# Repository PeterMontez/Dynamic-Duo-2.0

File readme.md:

# Web Application for a Tooling Storage System

Web application with the main goal of aiding people on the workshop to better keep up with the ever-changing position of their tools.

## About the project

Using EJS, JS and CSS, the application is very intuitive and simple to use, and alongside a RFID card reader allows the workers to remove or return tools to their correct cabinet and drawer.

Using mysql and sequelize to handle the data, the user can easily find the tool they want with very descriptive cards.
## Authors

- [@PeterMontez](https://github.com/PeterMontez)
- [@NycollasSobolevski](https://github.com/NycollasSobolevski)

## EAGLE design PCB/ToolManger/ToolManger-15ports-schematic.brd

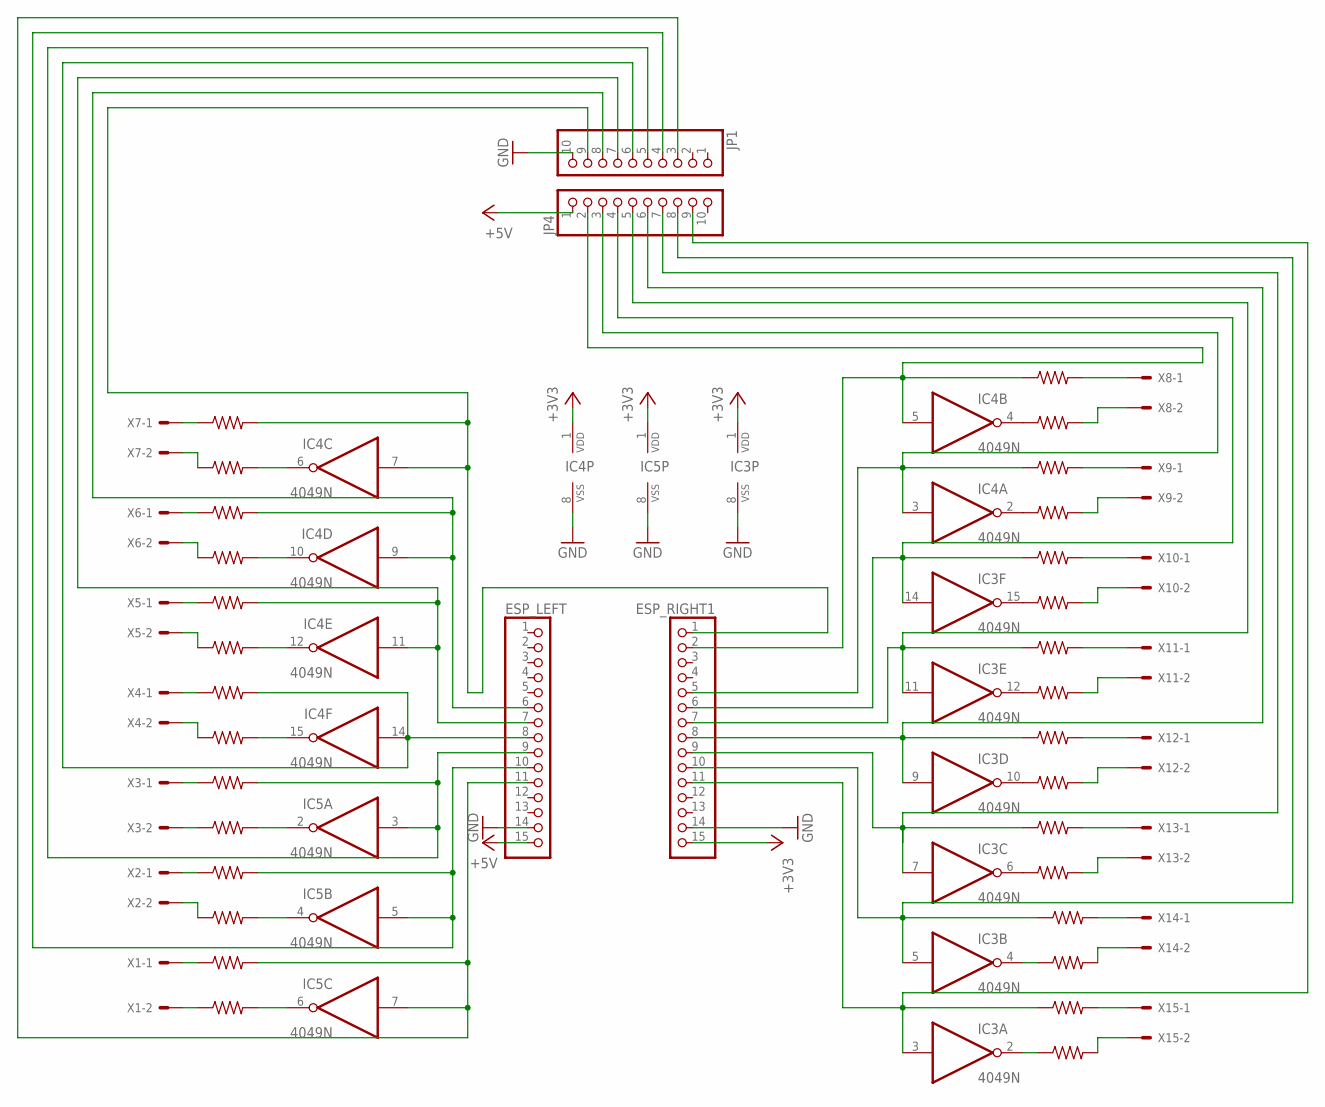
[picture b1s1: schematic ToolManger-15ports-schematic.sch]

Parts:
ESP_LEFT: PINHD-1X15; 1X15
ESP_RIGHT1: PINHD-1X15; 1X15
IC3, IC4, IC5: 4049N; DIL16
JP1, JP4: PINHD-1X10; 1X10
R1, R2, R3, R4, R5, R6, R7, R8, R9, R10, R11, R12, R13, R14, R15, R16, R17, R18, R19, R21, R22, R23, R24, R25, R26, R27, R28, R29, R30, R32: R-US_0207/12; 0207/12
X1, X2, X3, X4, X5, X6, X7, X8, X9, X10, X11, X12, X13, X14, X15: KK-156-2

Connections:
+3V3: ESP_RIGHT1.15, IC3.1 (VDD), IC4.1 (VDD), IC5.1 (VDD)
+5V: ESP_LEFT.15, JP4.1
GND: ESP_LEFT.14, ESP_RIGHT1.14, IC3.8 (VSS), IC4.8 (VSS), IC5.8 (VSS), JP1.10
unnamed: ESP_LEFT.6, IC4.9 (I), JP1.8, R30.2
unnamed: IC3.2 (O), R6.1
unnamed: R6.2, X15.2
unnamed: ESP_LEFT.7, IC4.11 (I), JP1.7, R18.2
unnamed: R18.1, X5.1
unnamed: R1.2, X15.1
unnamed: IC3.4 (O), R2.1
unnamed: R3.2, X14.1
unnamed: R2.2, X14.2
unnamed: ESP_RIGHT1.10, IC3.5 (I), JP4.8, R3.1
unnamed: IC3.6 (O), R4.1
unnamed: IC3.10 (O), R7.1
unnamed: IC3.15 (O), R11.1
unnamed: IC3.12 (O), R9.1
unnamed: R5.2, X13.1
unnamed: R4.2, X13.2
unnamed: R16.2, X8.1
unnamed: R8.2, X12.1
unnamed: R7.2, X12.2
unnamed: R9.2, X11.2
unnamed: R10.2, X11.1
unnamed: R11.2, X10.2
unnamed: R12.2, X10.1
unnamed: R13.2, X9.2
unnamed: R14.2, X9.1
unnamed: R15.2, X8.2
unnamed: ESP_RIGHT1.11, IC3.3 (I), JP4.9, R1.1
unnamed: IC4.2 (O), R13.1
unnamed: ESP_RIGHT1.9, IC3.7 (I), JP4.7, R5.1
unnamed: ESP_RIGHT1.8, IC3.9 (I), JP4.6, R8.1
unnamed: ESP_RIGHT1.7, IC3.11 (I), JP4.5, R10.1
unnamed: ESP_RIGHT1.6, IC3.14 (I), JP4.4, R12.1
unnamed: IC4.4 (O), R15.1
unnamed: ESP_RIGHT1.2, IC4.5 (I), JP4.2, R16.1
unnamed: ESP_RIGHT1.5, IC4.3 (I), JP4.3, R14.1
unnamed: ESP_LEFT.8, IC4.14 (I), JP1.6, R27.2
unnamed: ESP_LEFT.9, IC5.3 (I), JP1.5, R25.2
unnamed: ESP_LEFT.10, IC5.5 (I), JP1.4, R23.2
unnamed: ESP_LEFT.11, IC5.7 (I), JP1.3, R21.2
unnamed: ESP_RIGHT1.1, IC4.7 (I), JP1.9, R32.2
unnamed: R32.1, X7.1
unnamed: R21.1, X1.1
unnamed: IC4.6 (O), R19.2
unnamed: R23.1, X2.1
unnamed: R25.1, X3.1
unnamed: IC5.4 (O), R22.2
unnamed: IC5.2 (O), R24.2
unnamed: IC4.12 (O), R28.2
unnamed: R24.1, X3.2
unnamed: R27.1, X4.1
unnamed: R28.1, X5.2
unnamed: R29.1, X6.2
unnamed: R30.1, X6.1
unnamed: R19.1, X7.2
unnamed: IC4.10 (O), R29.2
unnamed: IC5.6 (O), R17.2
unnamed: IC4.15 (O), R26.2
unnamed: R26.1, X4.2
unnamed: R22.1, X2.2
unnamed: R17.1, X1.2

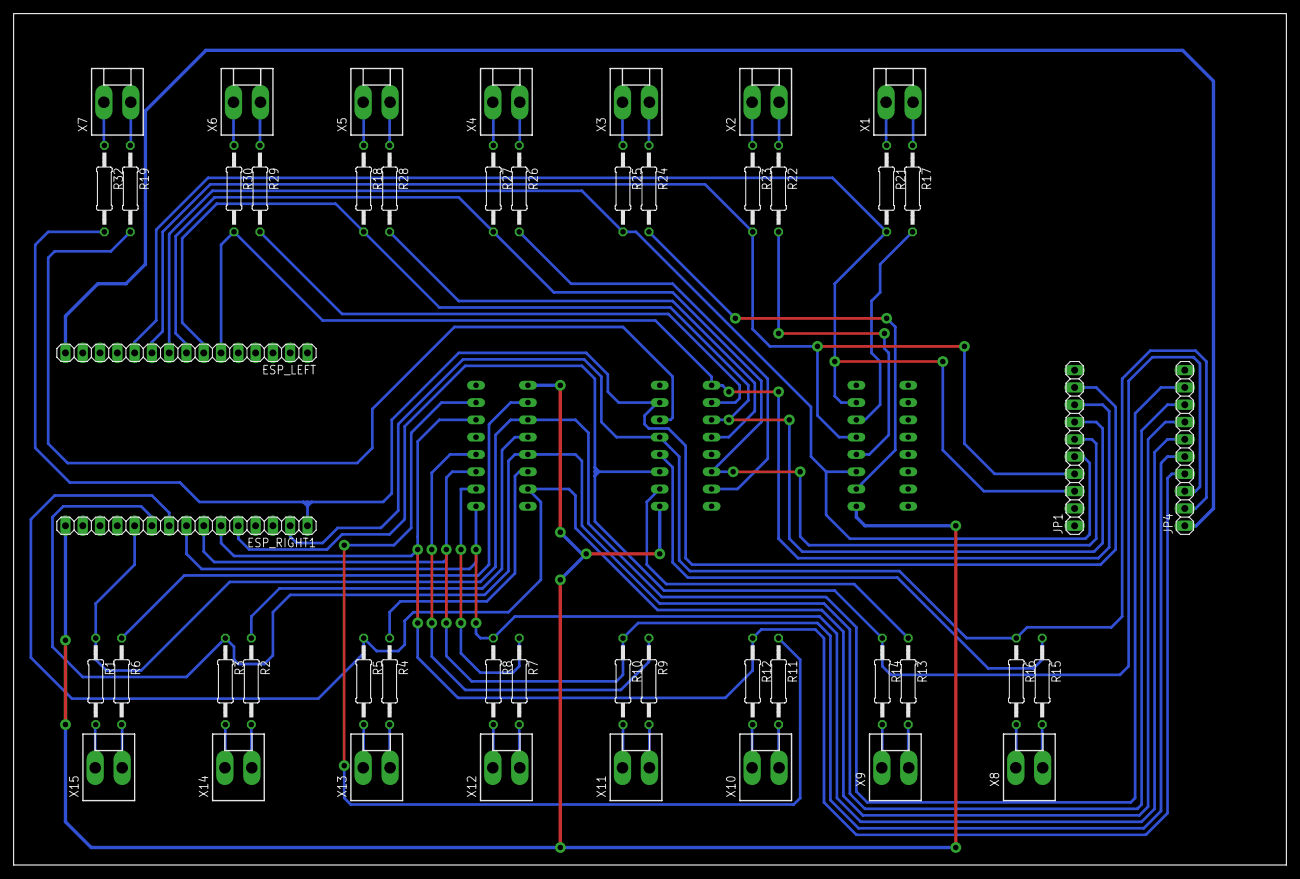
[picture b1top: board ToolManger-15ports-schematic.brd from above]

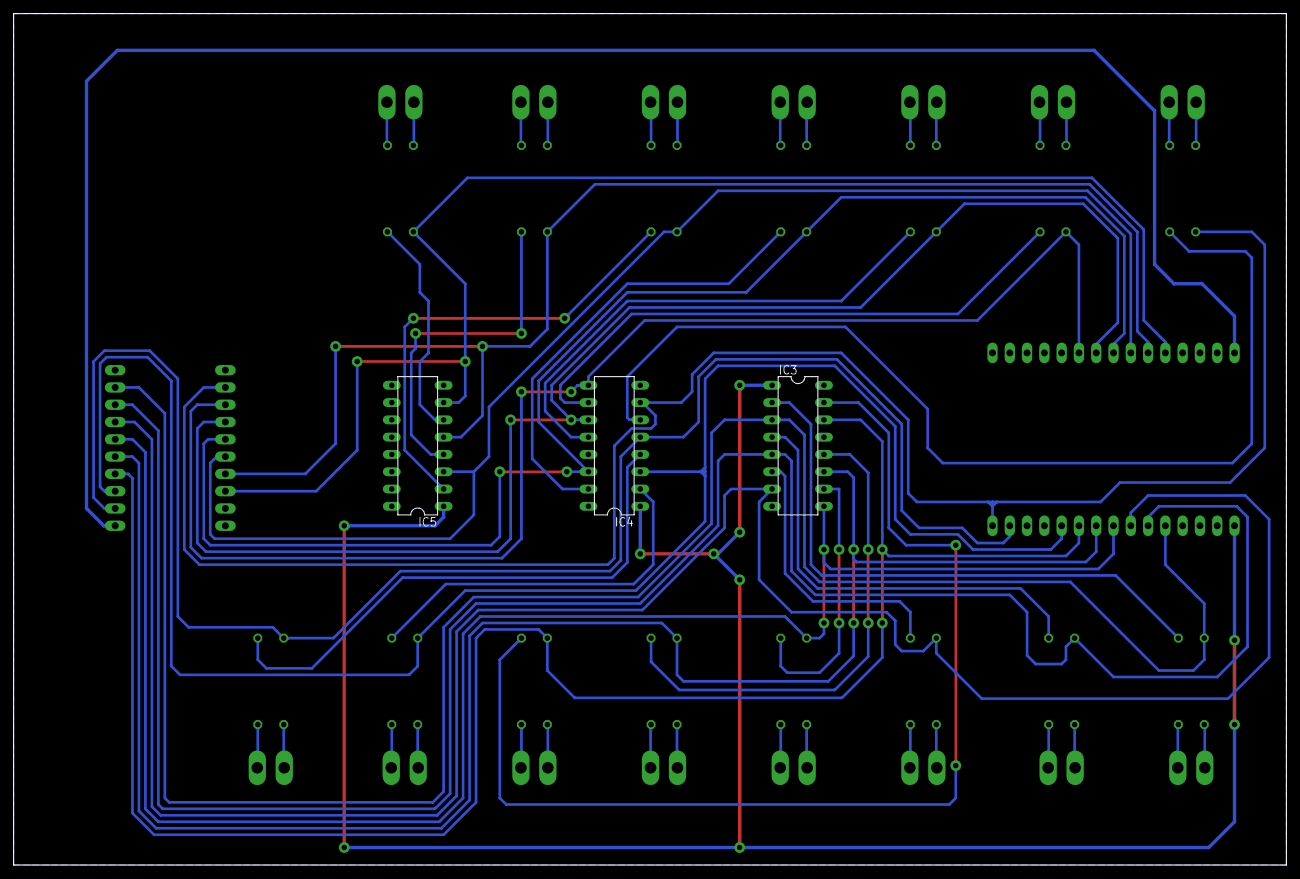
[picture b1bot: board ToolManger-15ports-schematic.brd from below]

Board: 2 copper layers, 187.0 x 125.1 mm, 52 parts (3 on the bottom side), 63 nets.

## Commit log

2023-01-23 Marco Zero
2023-01-23 ADD: Molde banco de dados
2023-01-24 ADD: first page, css and script
2023-01-24 Server
2023-01-24 ADD: views and public
2023-01-25 ADD: Pagina secundaria
2023-01-25 routes e front
2023-01-26 UPDATE: back and server started
2023-01-26 model pronto e controller iniciado
2023-01-26 controllers de select v1
2023-01-26 UPDATE: routes,home, indexjs (puxar card)
2023-01-26 controllers de cadastro e movimentacao de ferramenta
2023-01-26 routes atualizado
2023-01-26 ADD: Registration screen started(sem insert)
2023-01-27 UPDATE: Index
2023-01-27 home.js retorna listas para o front
2023-01-27 OBS: commitando so para dar push
2023-01-27 cadastro e routes atualizados
2023-01-27 UPDATE: style
2023-01-27 UPDATE: tela inicial concluida(por enquanto)
2023-01-27 devolver adicionado
2023-01-27 Pagina devolver adicionada
2023-01-27 UPDATE: Selects funcionando responsivamente
2023-01-27 UPDATE: Pegar equipamento semi funcionando
2023-01-30 bugfix edv retirada
2023-01-30 ADD: comecando ppagina pegar por ferramenta
2023-01-30 UPDATE: select do subtipo funcionando como deveria
2023-01-30 devolucao e retirada
2023-01-30 UPDATE: escolha por ferramenta
2023-01-30 devolução puxando dados
2023-01-30 sync
2023-01-30 colaboradores
2023-01-30 ADD: Colaboradores e ADMINS
2023-01-30 pagina de confirmacao
2023-01-30 ADD: cadastro por cracha
2023-01-30 UPDATE: retirar por cracha
2023-01-30 confirmacao concluida para devolver
2023-01-31 ADD: devolver com cartao
2023-01-31 telas de confirmacao
2023-01-31 merge, telas funcionando
2023-01-31 bugfix, inicio do edit
2023-01-31 comitando para dar pull
2023-02-01 UPDATE: pagina retirar funcionando com EDV
2023-02-01 UPDATE: Todas as entradas podem ser inderidas por EDV
2023-02-01 excluir em implementacao
2023-02-02 Comitando para sincronizar
2023-02-02 ADD: funcao editar
2023-02-02 excluir por ferramenta adicionado
2023-02-02 excluir finalizado
2023-02-02 UPDATE: tela Editar estilizada (faltando submit nas rotas)
2023-02-02 bugfix
2023-02-03 UPDATE: card ferramenta disabled qunado retirado
2023-02-03 excluir ferramenta funcionando de novo
2023-02-03 UPDATE: editar por ferramentas
2023-02-03 botao de voltar morreu
2023-02-03 voltar/excluir funcionando
2023-02-03 UPDATE: versao 1.0.0
2023-02-06 banco corrigido
2023-02-06 mais um update no banco de colaboradores
2023-02-06 update model
2023-02-06 ADD: return button
2023-02-06 final bugfix
2023-02-06 final commit
2024-08-27 update to prod
2024-08-27 ADD firebase on project
2024-08-29 ADD: code of IOT and UPDATE: file tree
2024-08-29 UPDATE: readme file
2024-08-30 UPDATE: conection for all ports
2024-09-02 ADD: board project
2024-09-03 UPDATE: board prototype finished
2024-09-04 ADD: flatcam file
2024-09-04 ADD: IOT esp datasheet and UPDATE: WEB connection with firebase when get tool
2024-09-05 UPDATE to deploy
2024-09-05 Release 1.2.0
